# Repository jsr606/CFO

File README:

source files for the CHEAP, FAT and OPEN project
===========================================================================
more info: http://8bitklubben.dk/project/CFO/
===========================================================================
in this repository you will find code for the CFO synth ("arduino" folder), the CFO tracker ("processing" folder), illustrator files for the acryl casing ("acrylic casing and lasercutter fix for PCB" folder), and CAD files for the hardware design ("eagle" folder)

sound code + hardware design in this project is based on the arduino synthesizer kit by critter and guittari: http://www.critterandguitari.com/content/arduino-synthesizer-kit

PLEASE NOTE:
this is a work in progress: all code and hardware design still consist bugs. dig the glitches! njam njam!

--- enjoy
          _____                    _____                   _______         
         /\    \                  /\    \                 /::\    \        
        /::\    \                /::\    \               /::::\    \       
       /::::\    \              /::::\    \             /::::::\    \      
      /::::::\    \            /::::::\    \           /::::::::\    \     
     /:::/\:::\    \          /:::/\:::\    \         /:::/~~\:::\    \    
    /:::/  \:::\    \        /:::/__\:::\    \       /:::/    \:::\    \   
   /:::/    \:::\    \      /::::\   \:::\    \     /:::/    / \:::\    \  
  /:::/    / \:::\    \    /::::::\   \:::\    \   /:::/____/   \:::\____\ 
 /:::/    /   \:::\    \  /:::/\:::\   \:::\    \ |:::|    |     |:::|    |
/:::/____/     \:::\____\/:::/  \:::\   \:::\____\|:::|____|     |:::|    |
\:::\    \      \::/    /\::/    \:::\   \::/    / \:::\    \   /:::/    / 
 \:::\    \      \/____/  \/____/ \:::\   \/____/   \:::\    \ /:::/    /  
  \:::\    \                       \:::\    \        \:::\    /:::/    /   
   \:::\    \                       \:::\____\        \:::\__/:::/    /    
    \:::\    \                       \::/    /         \::::::::/    /     
     \:::\    \                       \/____/           \::::::/    /      
      \:::\    \                                         \::::/    /       
       \:::\____\                                         \::/____/        
        \::/    /                                          ~~              
         \/____/

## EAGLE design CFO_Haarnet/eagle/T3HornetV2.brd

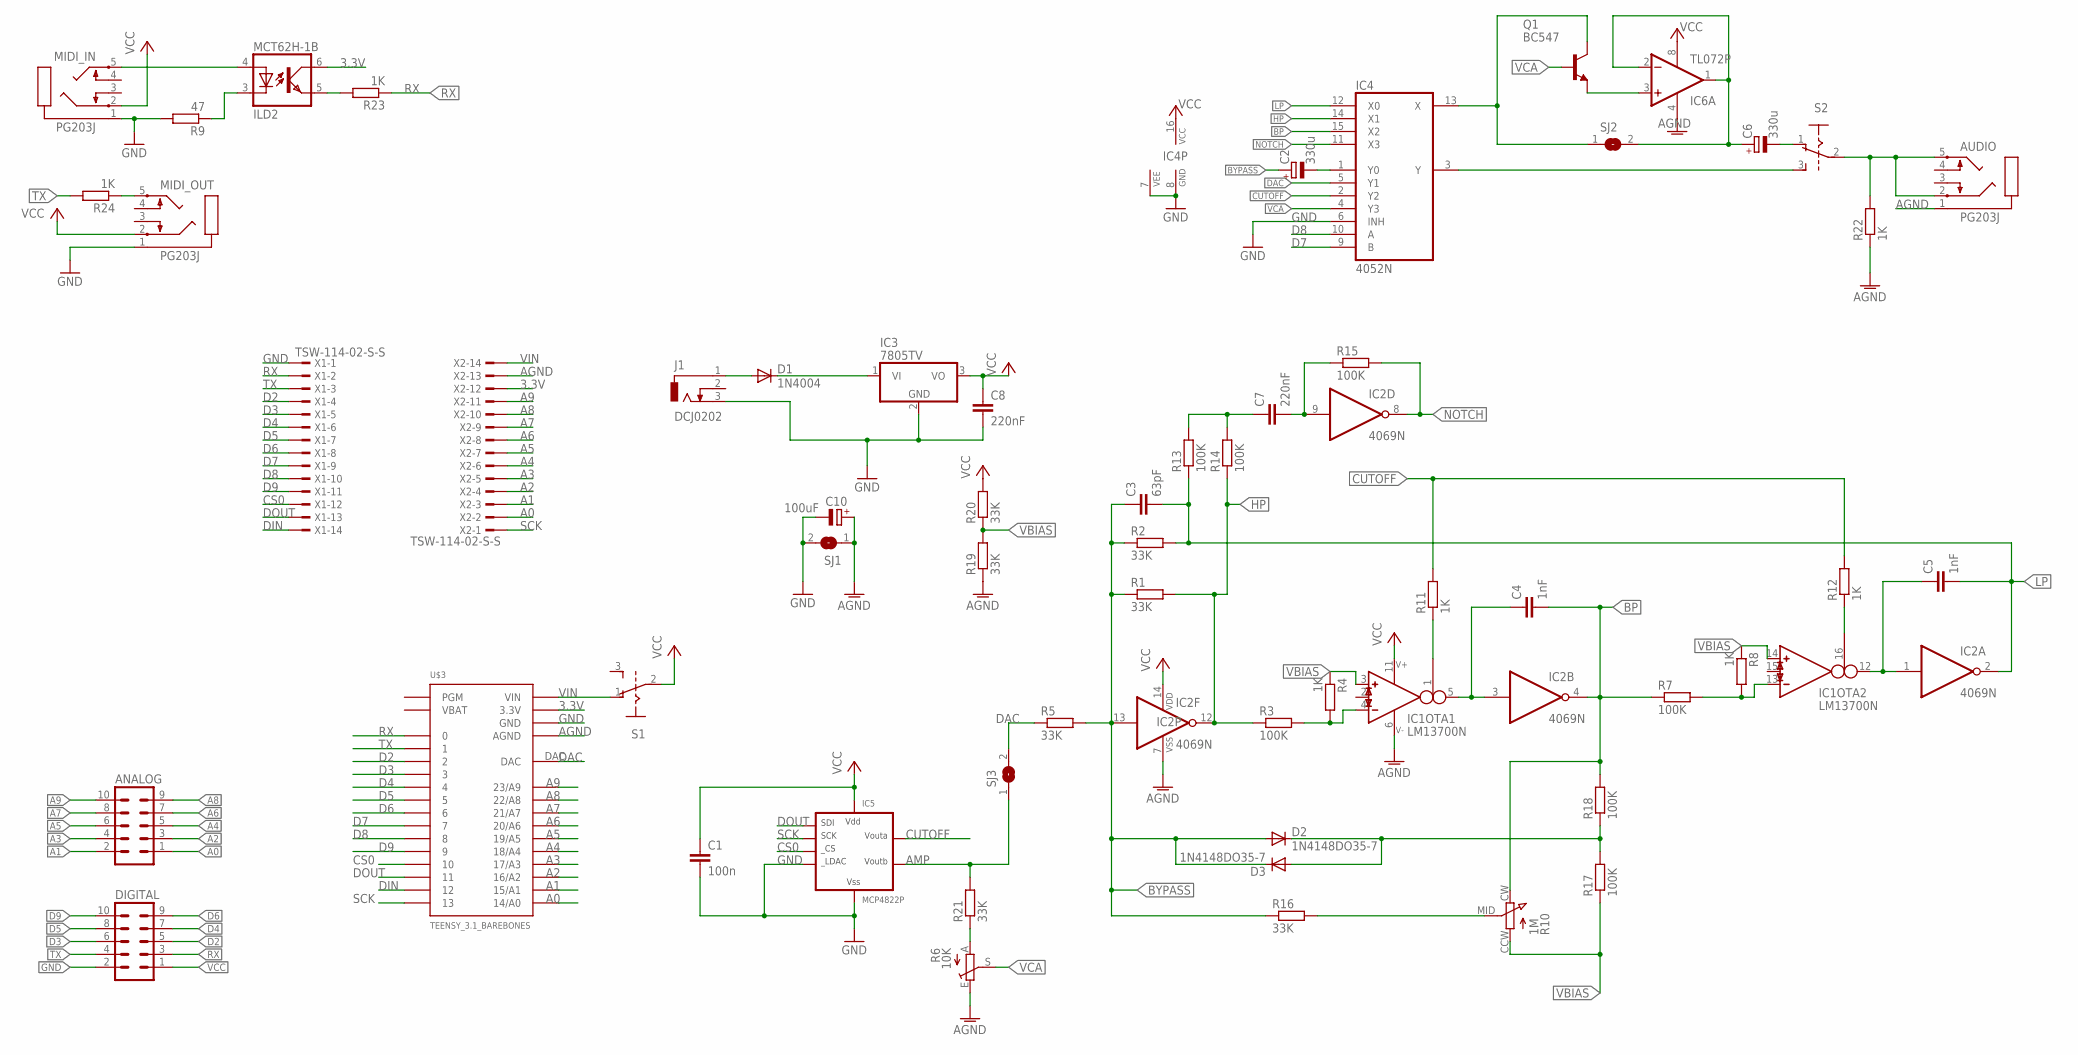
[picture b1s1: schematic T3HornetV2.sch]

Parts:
ANALOG: ML10
AUDIO: PG203J
C1: 100n; C050-030X075
C2, C6: 330u; E2,5-7
C3: 63pF; C025-024X044
C4, C5: 1nF; C025-024X044
C7, C8: 220nF; C050-030X075
C10: 100uF; E2,5-6
D1: 1N4004; DO41-10
D2, D3: 1N4148DO35-7; DO35-7
DIGITAL: ML10
IC1: LM13700N; DIL16
IC2: 4069N; DIL14
IC3: 7805TV; TO220V
IC4: 4052N; DIL16
IC5: MCP4822P; DIL8
IC6: TL072P; DIL08
J1: DCJ0202
MCT62H-1: ILD2; DIL08
MIDI_IN: PG203J
MIDI_OUT: PG203J
Q1: BC547; TO92
R1, R2, R5, R16, R19, R20, R21: 33K; 0207/7
R3, R7, R13, R14, R15, R17, R18: 100K; 0207/7
R4, R8, R11, R12, R22, R23, R24: 1K; 0207/7
R6: 10K; CA9V
R9: 47; 0207/7
R10: 1M; P120PK
S1, S2: EG1218; GF-126-0159
SJ1, SJ2, SJ3: SJ
U$3: TEENSY_3.1_BAREBONES
X1, X2: TSW-114-02-S-S

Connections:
3.3V: MCT62H-1.6 (COL), U$3.3.3V1 (3.3V), U$3.3.3V2 (3.3V), X2.12
A0: ANALOG.1, U$3.14/A0, X2.2
A1: ANALOG.2, U$3.15/A1, X2.3
A2: ANALOG.3, U$3.16/A2, X2.4
A3: ANALOG.4, U$3.17/A3, X2.5
A4: ANALOG.5, U$3.18/A4, X2.6
A5: ANALOG.6, U$3.19/A5, X2.7
A6: ANALOG.7, U$3.20/A6, X2.8
A7: ANALOG.8, U$3.21/A7, X2.9
A8: ANALOG.9, U$3.22/A8, X2.10
A9: ANALOG.10, U$3.23/A9, X2.11
AGND: AUDIO.1, C10.+, IC1.6 (V-), IC2.7 (VSS), IC6.4 (V-), R6.E, R19.1, R22.1, SJ1.1, U$3.AGND, X2.13
AMP: IC5.6 (VOUTB), R21.2, SJ3.1
BP: C4.2, IC2.4 (O), IC4.15 (X2), R7.1, R10.CW, R18.2
BYPASS: C2.+, C3.1, D2.A, D3.C, IC2.13 (I), R1.1, R2.1, R5.2, R16.1
CS0: IC5.2 (CS), U$3.10, X1.12
CUTOFF: IC4.2 (Y2), IC5.8 (VOUTA), R11.2, R12.2
D2: DIGITAL.5, U$3.2, X1.4
D3: DIGITAL.6, U$3.3, X1.5
D4: DIGITAL.7, U$3.4, X1.6
D5: DIGITAL.8, U$3.5, X1.7
D6: DIGITAL.9, U$3.6, X1.8
D7: IC4.9 (B), U$3.7, X1.9
D8: IC4.10 (A), U$3.8, X1.10
D9: DIGITAL.10, U$3.9, X1.11
DAC: IC4.5 (Y1), R5.1, SJ3.2, U$3.DAC
DIN: U$3.12, X1.14
DOUT: IC5.4 (SDI), U$3.11, X1.13
GND: C1.2, C8.2, C10.-, DIGITAL.2, IC3.2 (GND), IC4.6 (INH), IC4.7 (VEE), IC4.8 (GND), IC5.5 (LDAC), IC5.7 (VSS), J1.3, MIDI_IN.1, MIDI_OUT.1, R9.2, SJ1.2, U$3.GND1 (GND), U$3.GND2 (GND), X1.1
HP: IC2.12 (O), IC4.14 (X1), R1.2, R3.1, R14.1
LP: C3.2, C5.2, IC2.2 (O), IC4.12 (X0), R2.2, R13.1
unnamed: D1.A, J1.1
unnamed: IC6.3 (+IN), Q1.1 (E)
unnamed: D2.C, D3.A, R17.2, R18.1
unnamed: R6.A, R21.1
unnamed: IC1.4 (IN_N), R3.2, R4.2
unnamed: C6.-, S2.1
unnamed: C4.1, IC1.5 (OUT), IC2.3 (I)
unnamed: R10.MID, R16.2
unnamed: IC1.13 (IN_N), R7.2, R8.2
unnamed: IC4.3 (Y), S2.3
unnamed: C5.1, IC1.12 (OUT), IC2.1 (I)
unnamed: C7.2, IC2.9 (I), R15.1
unnamed: IC1.1 (I_BIAS), R11.1
unnamed: IC1.16 (I_BIAS), R12.1
unnamed: C7.1, R13.2, R14.2
unnamed: D1.C, IC3.1 (VI)
unnamed: C6.+, IC6.1 (OUT), IC6.2 (-IN), SJ2.2
unnamed: C2.-, IC4.1 (Y0)
unnamed: AUDIO.2, AUDIO.5, R22.2, S2.2
unnamed: IC4.13 (X), Q1.3 (C), SJ2.1
unnamed: MCT62H-1.5 (EMIT), R23.2
unnamed: MIDI_OUT.5, R24.1
unnamed: MCT62H-1.4 (A), MIDI_IN.5
unnamed: MCT62H-1.3 (C), R9.1
NOTCH: IC2.8 (O), IC4.11 (X3), R15.2
RX: DIGITAL.3, R23.1, U$3.0, X1.2
SCK: IC5.3 (SCK), U$3.13, X2.1
TX: DIGITAL.4, R24.2, U$3.1, X1.3
VBAT: U$3.VBAT
VBIAS: IC1.3 (IN_P), IC1.14 (IN_P), R4.1, R8.1, R10.CCW, R17.1, R19.2, R20.1
VCA: IC4.4 (Y3), Q1.2 (B), R6.S
VCC: C1.1, C8.1, DIGITAL.1, IC1.11 (V+), IC2.14 (VDD), IC3.3 (VO), IC4.16 (VCC), IC5.1 (VDD), IC6.8 (V+), MIDI_IN.2, MIDI_OUT.2, R20.2, S1.2
VIN: S1.1, U$3.VIN, X2.14

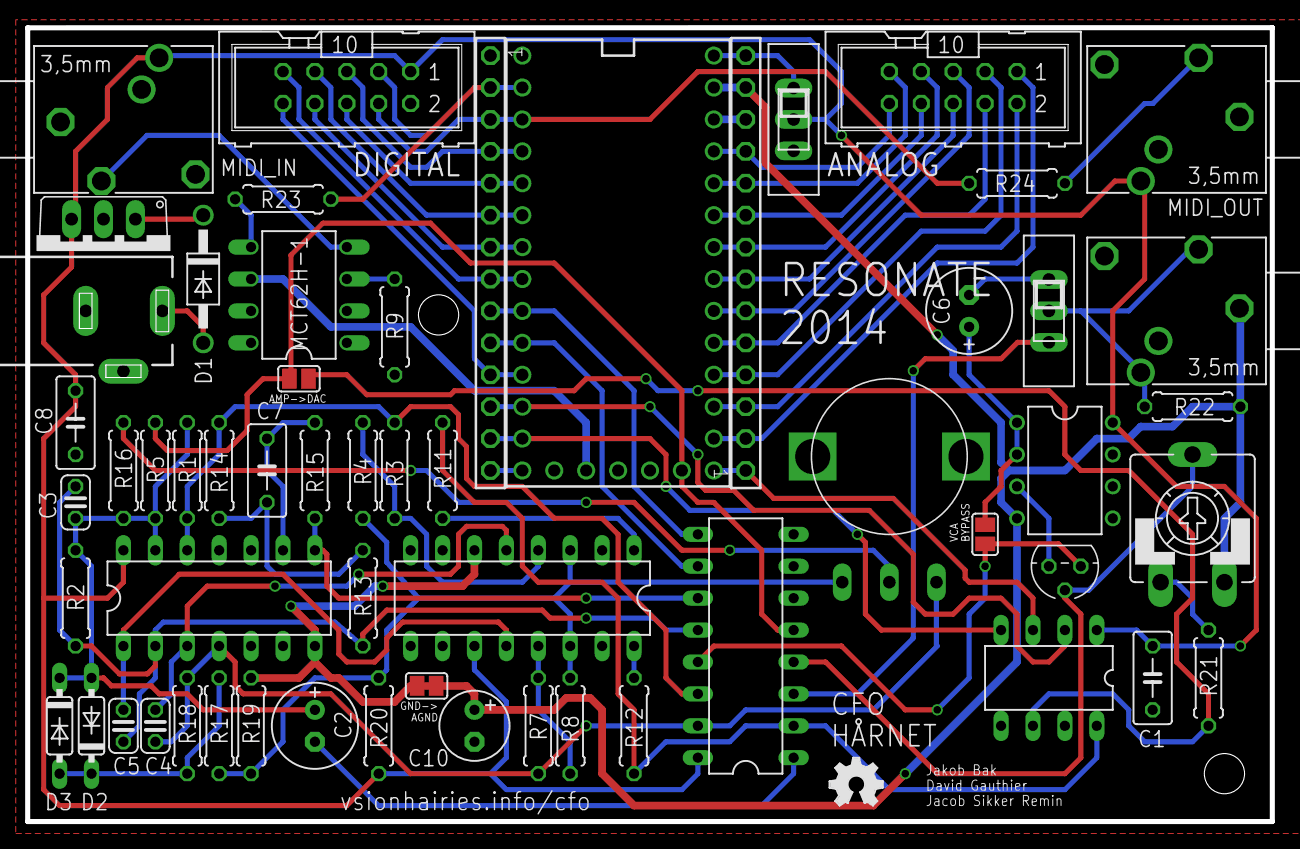
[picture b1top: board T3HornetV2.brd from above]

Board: 4 copper layers, 99.1 x 63.2 mm, 59 parts (0 on the bottom side), 63 nets.

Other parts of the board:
U$1: OSHW_FILLX150_NOTEXT

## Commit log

2011-05-18 ASCII
2011-05-18 IMAC code and MFRU edition hardware
2011-10-07 tracker software now listens to incoming MIDI
    the tracker is now listening for incoming MIDI on for instance the IAC
    driver in OS X. incoming MIDI is forwarded as serial commands to the CFO
2011-10-08 .pdf files for lasercutting acrylic casing added
    the .pdf files include several layers and are illustrator editable
2011-10-08 small readme changes
2011-10-08 added bill of materials to eagle files
2011-10-08 picture explaining button layout and controls
2013-12-18 Changed folder structure to reflect CFO family
2013-12-18 added uCFO lib
2013-12-18 Added processing CFO Dashboard
2013-12-18 Updated example files and processing dashboard
2013-12-19 disabled filter to free up cycles, added cheatsheet
2013-12-19 Updated keywords and cheat sheet
2014-03-07 Added Haarnet to CFO library
2014-03-07 Changed SPI method and upped sample rate to 48KHz
2014-03-24 Added a files to documentation and fixed some minor sound issues
2014-03-29 Split code into Synth.h, Synth.cpp
2014-03-30 Cleaned up some unused functions
2014-04-02 working on preset loading and saving
2014-04-02 Presetting almost done
2014-04-02 NEW README
    moved the old CFO readme
2014-04-02 sensor test sketch
    w/ processing graphing sketch
2014-04-02 tweaked serial_grapher_for_haarnet_sensors
2014-04-02 Presets almost finally there totally :)
2014-04-02 Presets done!
2014-04-02 added sequencer in library
2014-04-03 Updated cheat sheet
2014-04-03 tweaked sequencer
2014-04-03 updated Haarnet_init_midi
2014-04-03 Added eagle and gerber files
2014-04-18 randomize presets function
    added a function to recall presets while randomizing them
2014-04-18 experimental code folder
    new folder with experimental / temp code
    now containing sketch recalling / saving presets with the new
    getRandomizedPreset() function
2014-04-19 non-commit
2014-04-19 sampler
2014-04-19 fixed malloc / memset in Sampler
2014-05-13 Added hardware serial for MIDI
2014-05-13 a few experimental .ino instruments from nantes
2014-05-13 fixed small github mess up
2014-05-13 Fixed init midi example sketch
2014-06-14 Sequencer sample added to experimental
2014-06-14 glitch you git
2014-06-15 added bodyseq folder
2014-06-15 Added files to bodyseq
2014-06-15 Renamed BODYSEQ folder
2014-06-15 Moved library files to libraries folder
2014-06-15 moved BODYSEQ library folder
2014-06-15 added assembly instructions
2014-06-15 Disabled mcp4251
2014-06-15 put comments to assembly tutorial in txt file
2014-06-19 text files for relevant links
2014-06-19 first interactive sequencer code up and running
2014-06-23 updated sequencer, added manual, updated assembly instructions
2014-06-24 sequencer updated
2014-06-24 moved oscil variables to public
2014-06-24 added jacob's example to example folder
2014-06-25 updated sequencer, moved to official examples, updated assembly instruction
2014-06-28 updated manual and added BOM
2014-06-30 added MAX/MSP dashboard
2014-06-30 MAX/MXP dashboard fixes
2014-06-30 added README to CFO BODYSEQ w/ upverter link
2014-07-07 added earlier stages of other filter types.
    other filter types not ready yet
2014-07-24 added new filter type
2014-07-24 Added phaseDistortion Oscillator
2014-07-25 changes to vectorOscillator
2014-07-27 Added CFO_BODYSEQ_V2.ino in examples
2014-07-28 added note on uploading code to teensy based CFOs to documentation
2014-08-08 Added type of resonance to LP24 filter implementation
2014-08-12 Temporary changes
2014-10-04 updated documentation + BOM for 3-button version
2014-10-04 word temp file deleted
2014-10-05 better manual
2014-10-11 Moved usbMIDI interface functions to Haarnet.h, added example
2014-10-14 reworked navigation for 2 button BODYSEQ
2014-10-14 Fixed BodyseqSynth.cpp wrong DAC
2014-10-15 cleaned up sequencer code, 2 versions working
    much better interaction. support for both 2 and 3 button version.
2014-10-15 cleaned up and updated documentation
2014-10-19 Small update to Sequencer.h to improve stability
2014-10-19 renamed old Sequencer.h and .cpp as _v1
2014-10-20 Updated sequencer functionality in Haarnet
2014-10-20 Updated uCFO to work with newer code (filters, etc)
2014-10-20 Added "sequenced_audio2" example
2014-10-23 renaming / moscow sketches
2014-10-27 Haarnet Flute Extension
2014-10-27 clean up haarnet lib/examples
2014-11-04 Added CFO_BODYSEQ_v2b gerber files
    and updated the sequenced_audio examples in uCFO examples folder
2014-11-04 experimental haarnet code
2014-12-29 new experimentals
    arpeggiator and MIDI controller
2014-12-29 new experimentals
    max/msp patch for MIDI controller
2015-01-10 changed number of user presets to 8
2015-01-10 readme
    updated readme
2015-01-12 BOM 2 button version small fixes
2015-01-13 Added note sequencers to library
2015-01-13 Added MIDI Clock
2015-01-13 Added routing for MIDI In/Out and Clock
2015-02-20 updated read me
2015-02-20 Updated readme again
2015-03-29 made copy of example file with small changes
2015-03-30 Fixed bug with _begin randomly setting to large negative number
2015-03-30 started adding MIDI support for Sequencer
2015-06-17 minor changes to BODYSEQ files
2015-06-24 midi sync kinda there
2015-06-24 fixed number of presets to 16
2015-08-07 commented out some sequencer midi commands that clashes with presets
2015-08-07 new experimental arp mode with real sequencer lib
2015-08-08 added samples - try sampler sketch in examples folder
2015-09-03 new play mode: arpeggiator
2015-09-03 added pdf version of documentation
2015-09-04 uploaded new samples
2015-09-04 better arp sketch
2015-09-28 SAMPLER IS HERE!!!!! FIRE IT UP!!!!!
2015-09-30 copy track, clear track, chain track, EEPROM, bit crusher
2016-01-19 deleted hidden OS X
2016-04-05 small stuffs, LED feedback on MIDI note in (added, then uncommented)
2018-04-10 added envelope multiplier to bodyseq lib and midi feedback
2018-04-10 added debug code to easily check if hardware (interface) is working
2018-04-11 insert control panel preview image
2018-04-11 new arp mode in experimentals
2018-04-11 preview image
2018-04-11 readme should be markdown
2018-04-11 experimental: new arp mode
2018-04-11 changed some preset sounds and added EEPROM utility to quickly store some user presets
2018-06-04 more utilities
2018-06-04 add dumpAllPresets
